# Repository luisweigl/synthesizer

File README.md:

# Synthesizer

In this project, I try to build my own digital synthesizer.

## Software

This repository contains the C++ code for the full synthesizer. Only MIDI input and audio output libraries are used.
Currently, this codebase runs on Linux using the JACK audio API, but the goal is for it to run on a Teensy 4.1 Microcontroller.

## Hardware

Additionally, I want to build a complete, functioning synthesizer on which this code can be run.
The synthesizer should contain all necessary instruments to make cool sounds, that means multiple Oscillators, Filtering, Envelope Settings, etc.

Under `/PCB` is the KiCad project for the custom PCB that I want to design and build for the synthesizer.
The casing should later be 3D printed.

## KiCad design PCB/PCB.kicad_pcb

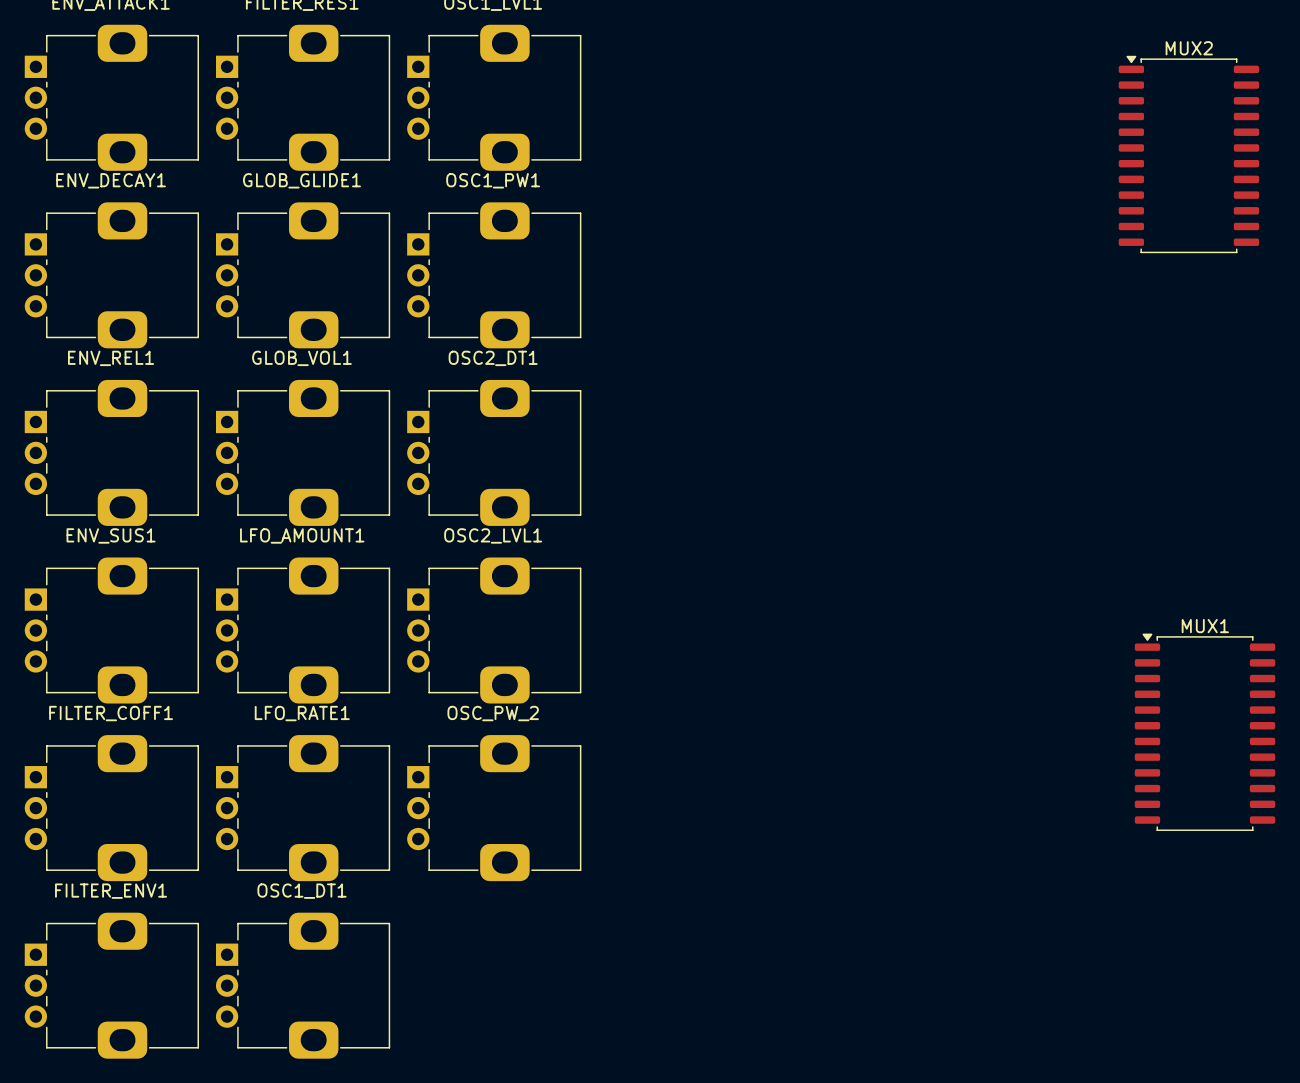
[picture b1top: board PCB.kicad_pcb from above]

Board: 2 copper layers, 19 parts (0 on the bottom side), 23 nets, no tracks yet.

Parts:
ENV_ATTACK1: 10k; Potentiometer_Alps_RK09K_Single_Vertical
ENV_DECAY1: 10k; Potentiometer_Alps_RK09K_Single_Vertical
ENV_REL1: 10k; Potentiometer_Alps_RK09K_Single_Vertical
ENV_SUS1: 10k; Potentiometer_Alps_RK09K_Single_Vertical
FILTER_COFF1: 10k; Potentiometer_Alps_RK09K_Single_Vertical
FILTER_ENV1: 10k; Potentiometer_Alps_RK09K_Single_Vertical
FILTER_RES1: 10k; Potentiometer_Alps_RK09K_Single_Vertical
GLOB_GLIDE1: 10k; Potentiometer_Alps_RK09K_Single_Vertical
GLOB_VOL1: 10k; Potentiometer_Alps_RK09K_Single_Vertical
LFO_AMOUNT1: 10k; Potentiometer_Alps_RK09K_Single_Vertical
LFO_RATE1: 10k; Potentiometer_Alps_RK09K_Single_Vertical
MUX1, MUX2: CD74HC4067M; SOIC-24W_7.5x15.4mm_P1.27mm
OSC1_DT1, OSC1_LVL1, OSC1_PW1, OSC2_DT1, OSC2_LVL1: 10k; Potentiometer_Alps_RK09K_Single_Vertical
OSC_PW_2: 10k; Potentiometer_Alps_RK09K_Single_Vertical

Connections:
/3V3: ENV_ATTACK1.3, ENV_DECAY1.3, ENV_REL1.3, ENV_SUS1.3, FILTER_COFF1.3, FILTER_ENV1.3, FILTER_RES1.3, GLOB_GLIDE1.3, GLOB_VOL1.3, LFO_AMOUNT1.3, LFO_RATE1.3, MUX1.24 (VCC), MUX2.24 (VCC), OSC1_DT1.3, OSC1_LVL1.3, OSC1_PW1.3, OSC2_DT1.3, OSC2_LVL1.3, OSC_PW_2.3
/ENV_ATTACK_IN: ENV_ATTACK1.2, MUX2.16 (I15)
/ENV_DECAY_IN: ENV_DECAY1.2, MUX2.17 (I14)
/ENV_REL_IN: ENV_REL1.2, MUX2.19 (I12)
/ENV_SUS_IN: ENV_SUS1.2, MUX2.18 (I13)
/FILTER_COFF_IN: FILTER_COFF1.2, MUX1.5 (I4)
/FILTER_ENV_IN: FILTER_ENV1.2, MUX1.7 (I2)
/FILTER_RES_IN: FILTER_RES1.2, MUX1.6 (I3)
/GLOB_GLIDE_IN: GLOB_GLIDE1.2, MUX2.3 (I6)
/GLOB_VOL_IN: GLOB_VOL1.2, MUX2.2 (I7)
/GND: ENV_ATTACK1.1, ENV_DECAY1.1, ENV_REL1.1, ENV_SUS1.1, FILTER_COFF1.1, FILTER_ENV1.1, FILTER_RES1.1, GLOB_GLIDE1.1, GLOB_VOL1.1, LFO_AMOUNT1.1, LFO_RATE1.1, MUX1.12 (GND), MUX1.15 (~E), MUX2.12 (GND), MUX2.15 (~E), OSC1_DT1.1, OSC1_LVL1.1, OSC1_PW1.1, OSC2_DT1.1, OSC2_LVL1.1, OSC_PW_2.1
/LFO_AMOUNT_IN: LFO_AMOUNT1.2, MUX2.21 (I10)
/LFO_RATE_IN: LFO_RATE1.2, MUX2.20 (I11)
/MUX_S0: MUX1.10 (S0), MUX2.10 (S0)
/MUX_S1: MUX1.11 (S1), MUX2.11 (S1)
/MUX_S2: MUX1.14 (S2), MUX2.14 (S2)
/MUX_S3: MUX1.13 (S3), MUX2.13 (S3)
/OSC1_DT_IN: MUX1.18 (I13), OSC1_DT1.2
/OSC1_LVL_IN: MUX1.20 (I11), OSC1_LVL1.2
/OSC1_PW_IN: MUX1.19 (I12), OSC1_PW1.2
/OSC2_DT_IN: MUX1.23 (I8), OSC2_DT1.2
/OSC2_LVL_IN: MUX1.3 (I6), OSC2_LVL1.2
/OSC2_PW_IN: MUX1.2 (I7), OSC_PW_2.2
